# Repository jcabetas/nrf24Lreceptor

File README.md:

# alimentador
Alimentador con STM32 y baterías
# nrf24Lreceptor
# nrf24Lreceptor

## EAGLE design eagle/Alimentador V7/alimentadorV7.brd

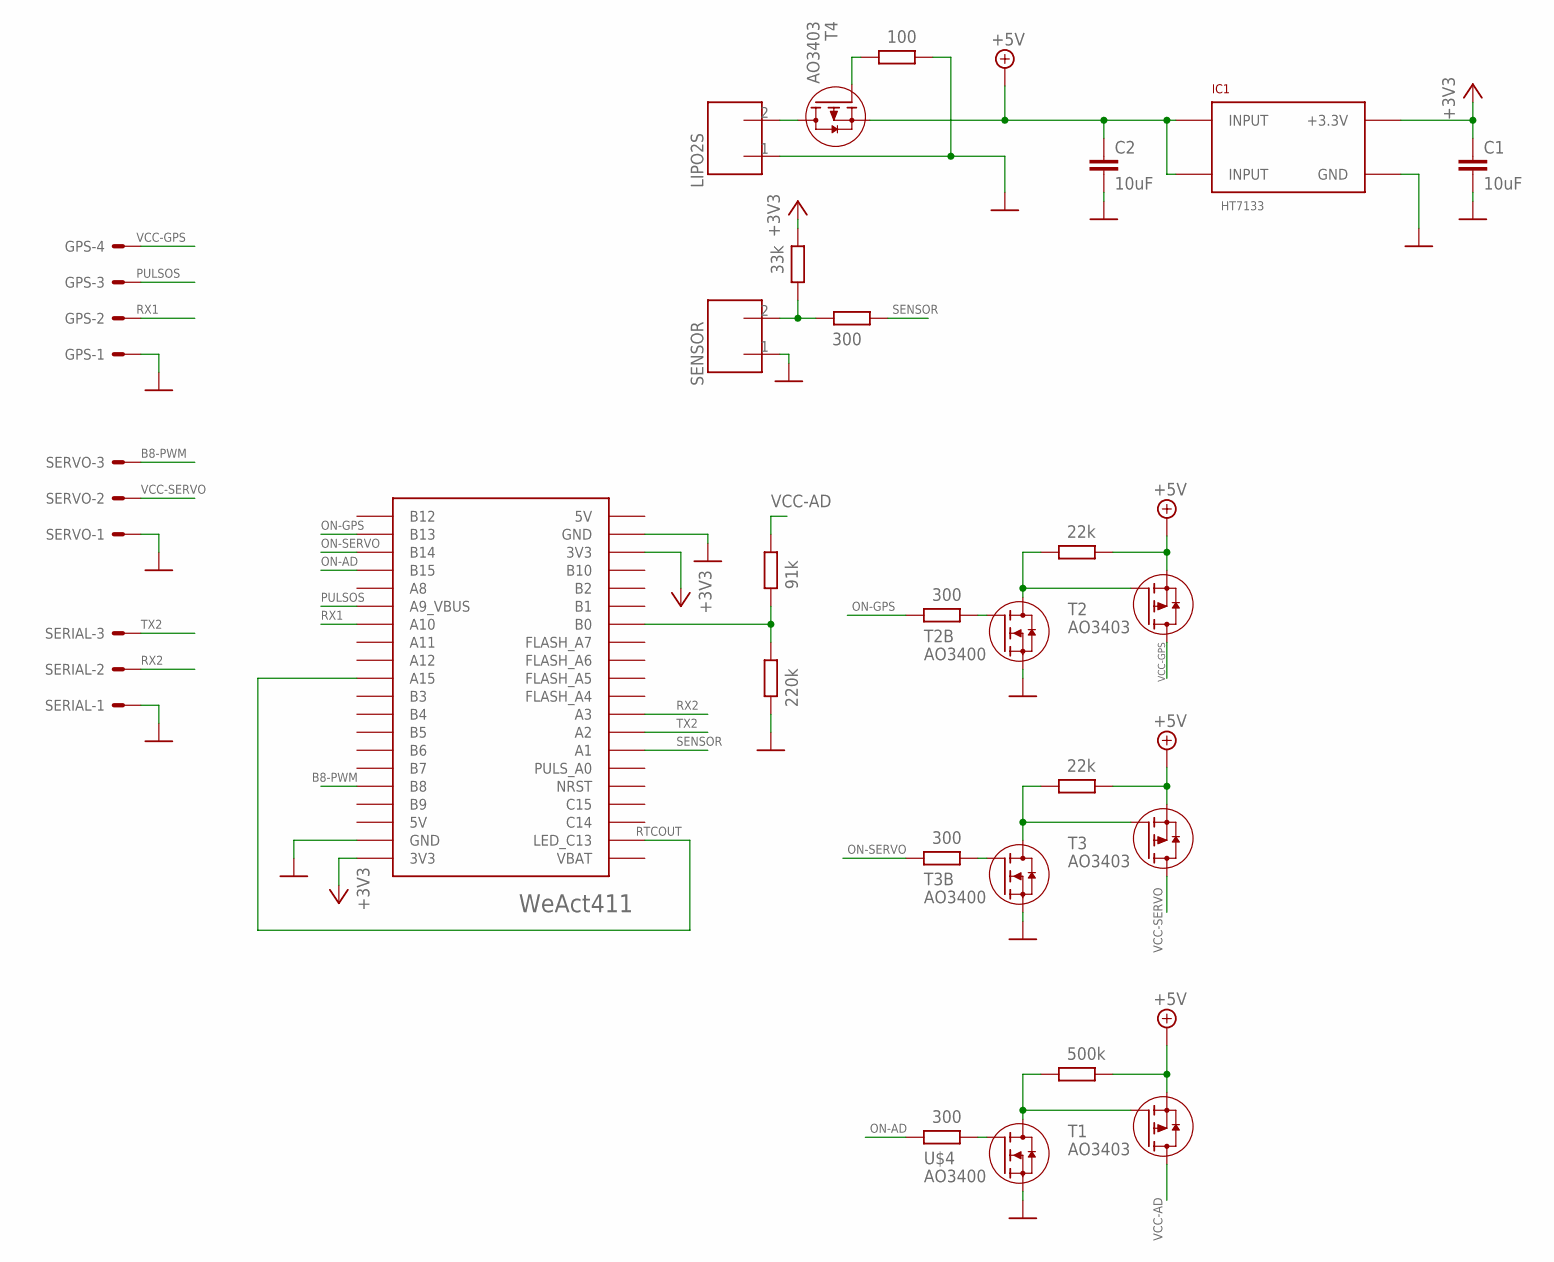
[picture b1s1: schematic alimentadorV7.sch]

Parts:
C1, C2: 10uF; C1206
GPS: 22-23-2041
IC1: HT7133; SOT89
LIPO2S: CONECTOR_2P-3.81; CON2P-3.81
R1, R5: 22k; R1206
R2: 220k; R1206
R3: 91k; R1206
R4, R6, R10: 300; R1206
R7: 100; R1206
R9: 33k; R1206
R11: 500k; R1206
SENSOR: CONECTOR_2P-3.81; CON2P-3.81
SERIAL: 22-23-2031
SERVO: 22-23-2031
T1, T2, T3, T4: AO3403; SOT23
T1B: 300; R1206
T2B, T3B: AO3400; SOT23
U$2: WEACT411
U$4: AO3400; SOT23

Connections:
+3V3: C1.1, IC1.3 (+3.3V), R9.2, U$2.3V3@1 (3V3), U$2.3V3@2 (3V3)
+5V: C2.1, IC1.2 (INPUT), IC1.4 (INPUT), R1.2, R5.2, R11.2, T1.2 (S), T2.2 (S), T3.2 (S), T4.2 (S)
B8-PWM: SERVO.3, U$2.B8
GND: C1.2, C2.2, GPS.1, IC1.1 (GND), LIPO2S.1, R2.2, R7.2, SENSOR.1, SERIAL.1, SERVO.1, T2B.2 (S), T3B.2 (S), U$2.GND@1 (GND), U$2.GND@2 (GND), U$4.2 (S)
unnamed: LIPO2S.2, T4.3 (D)
unnamed: R2.1, R3.2, U$2.B0
unnamed: R7.1, T4.1 (G)
unnamed: U$2.A15, U$2.C13 (LED_C13)
unnamed: R1.1, T2.1 (G), T2B.3 (D)
unnamed: R11.1, T1.1 (G), U$4.3 (D)
unnamed: R4.2, T2B.1 (G)
unnamed: R5.1, T3.1 (G), T3B.3 (D)
unnamed: R9.1, R10.2, SENSOR.2
unnamed: R6.2, T3B.1 (G)
unnamed: T1B.2, U$4.1 (G)
ON-AD: T1B.1, U$2.B15
ON-GPS: R4.1, U$2.B13
ON-SERVO: R6.1, U$2.B14
PULSOS: GPS.3, U$2.A9 (A9_VBUS)
RX1: GPS.2, U$2.A10
RX2: SERIAL.2, U$2.A3
SENSOR: R10.1, U$2.A1
TX2: SERIAL.3, U$2.A2
VCC-AD: R3.1, T1.3 (D)
VCC-GPS: GPS.4, T2.3 (D)
VCC-SERVO: SERVO.2, T3.3 (D)

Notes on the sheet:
RTCOUT

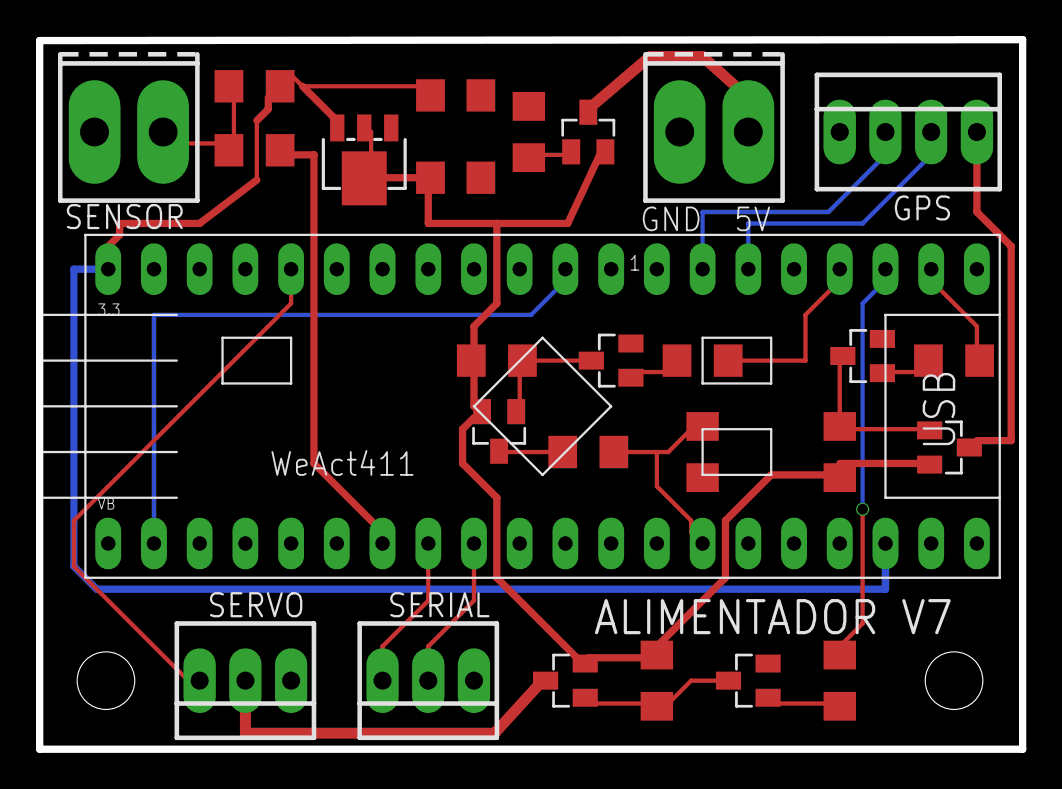
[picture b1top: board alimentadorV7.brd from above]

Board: 2 copper layers, 54.6 x 39.4 mm, 27 parts (0 on the bottom side), 26 nets.

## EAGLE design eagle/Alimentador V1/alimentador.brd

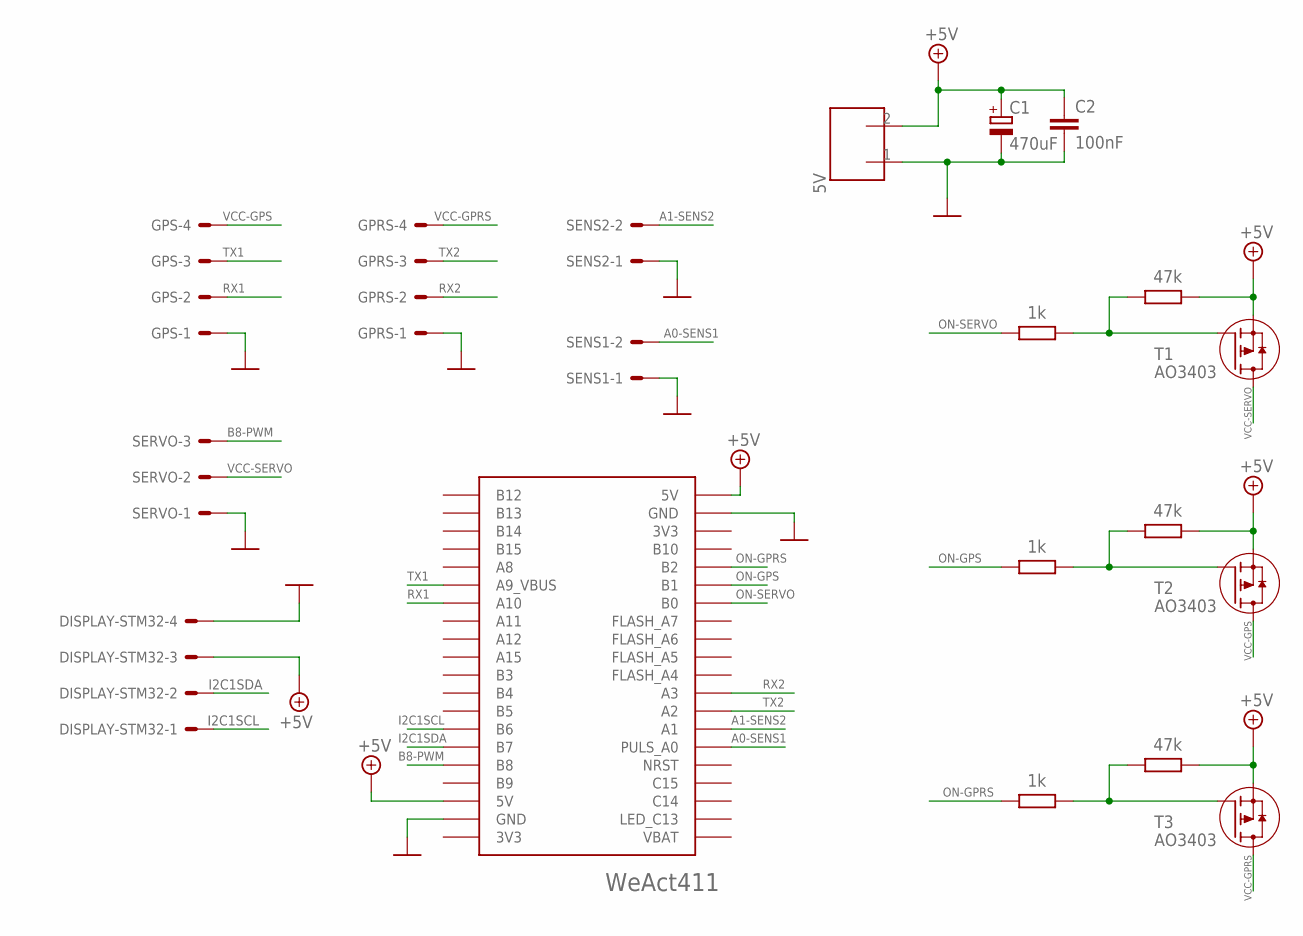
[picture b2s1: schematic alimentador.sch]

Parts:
5V: CONECTOR_2P-3.81; CON2P-3.81
C1: 470uF; E5-10,5
C2: 100nF; C1206
DISPLAY-STM32: 22-05-7048-04; 7395-04
GPRS: 22-27-2041-04; 6410-04
GPS: 22-27-2041-04; 6410-04
R1, R2, R5: 47k; R1206
R3, R4, R6: 1k; R1206
SENS1, SENS2: 22-27-2021-02; 6410-02
SERVO: 22-27-2031-03; 6410-03
T1, T2, T3: AO3403; SOT23
U$2: WEACT411

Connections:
+5V: 5V.2, C1.+, C2.1, DISPLAY-STM32.3, U$2.5V@1 (5V), U$2.5V@2 (5V)
A0-SENS1: SENS1.2, U$2.A0 (PULS_A0)
A1-SENS2: SENS2.2, U$2.A1
B8-PWM: SERVO.3, U$2.B8
GND: 5V.1, C1.-, C2.2, DISPLAY-STM32.4, GPRS.1, GPS.1, SENS1.1, SENS2.1, SERVO.1, U$2.GND@1 (GND), U$2.GND@2 (GND)
I2C1SCL: DISPLAY-STM32.1, U$2.B6
I2C1SDA: DISPLAY-STM32.2, U$2.B7
unnamed: R2.2, T1.2 (S)
unnamed: R2.1, R3.2, T1.1 (G)
unnamed: R1.2, T2.2 (S)
unnamed: R1.1, R4.2, T2.1 (G)
unnamed: R5.2, T3.2 (S)
unnamed: R5.1, R6.2, T3.1 (G)
ON-GPRS: R6.1, U$2.B2
ON-GPS: R4.1, U$2.B1
ON-SERVO: R3.1, U$2.B0
RX1: GPS.2, U$2.A10
RX2: GPRS.2, U$2.A3
TX1: GPS.3, U$2.A9 (A9_VBUS)
TX2: GPRS.3, U$2.A2
VCC-GPRS: GPRS.4, T3.3 (D)
VCC-GPS: GPS.4, T2.3 (D)
VCC-SERVO: SERVO.2, T1.3 (D)

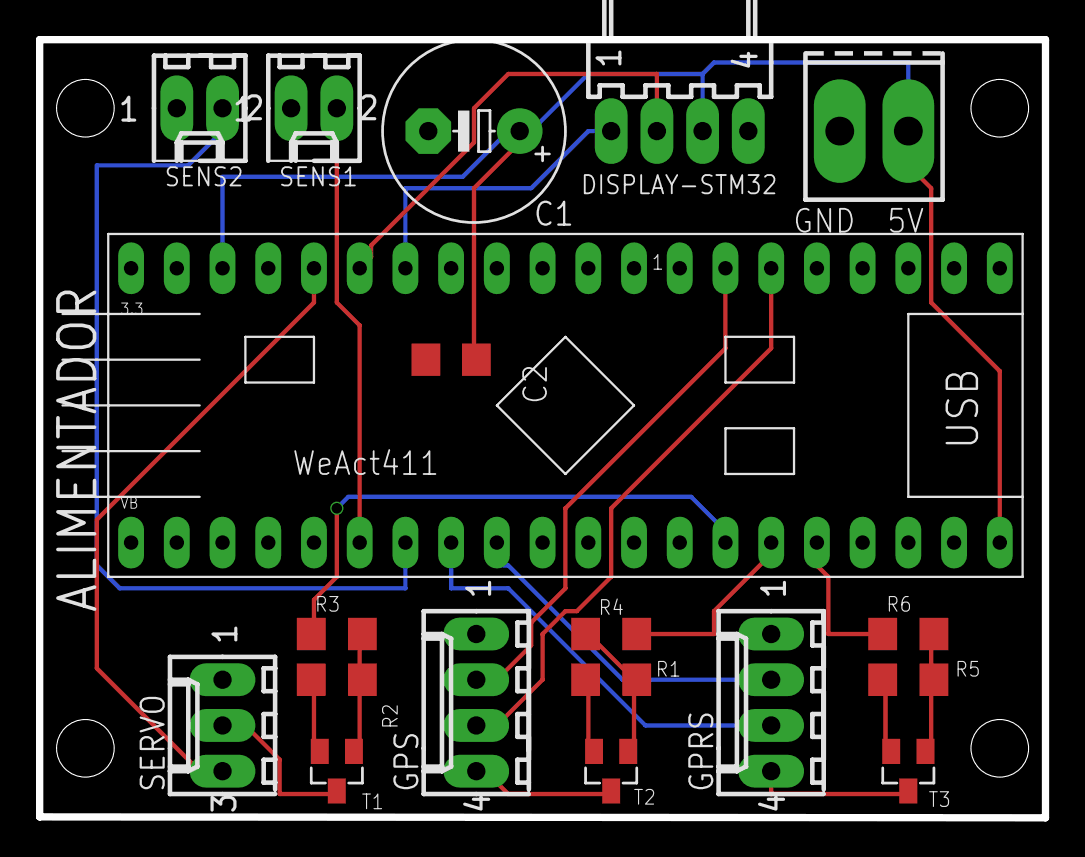
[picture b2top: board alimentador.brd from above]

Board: 2 copper layers, 55.9 x 43.2 mm, 19 parts (0 on the bottom side), 23 nets.

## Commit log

2024-03-07 Se conecta
2024-03-08 Funcionando NRF24
2024-03-08 Limpieza de codigo, servo y eeprom funcionando
2024-03-11 Funcionando
